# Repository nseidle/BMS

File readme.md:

Battery Management System
=======

This is a breakout board for the BQ76940. This configuration allows for 15 cells to be read. There is no safety cut off.

This is a dangerous board that exposes the user to over 48VDC and many amps. Please use responsibly.

v1 of the board is functional. Firmware is working. Most functions are written. 

-> v2 of the board has full cutoff MOSFETs and charging MOSFETs. <-

v1 of the test pack works but has multiple errors that are fixed on v2. Number labels on the cells are reversed. Cells 9 and 14 were shorted to bring the voltage back down to 48V. The clips are very close together so plastic insulators were glued in place.

License Information
-------------------

This code is public domain but you buy me a beer if you use this and we meet someday ([Beerware license](http://en.wikipedia.org/wiki/Beerware)).

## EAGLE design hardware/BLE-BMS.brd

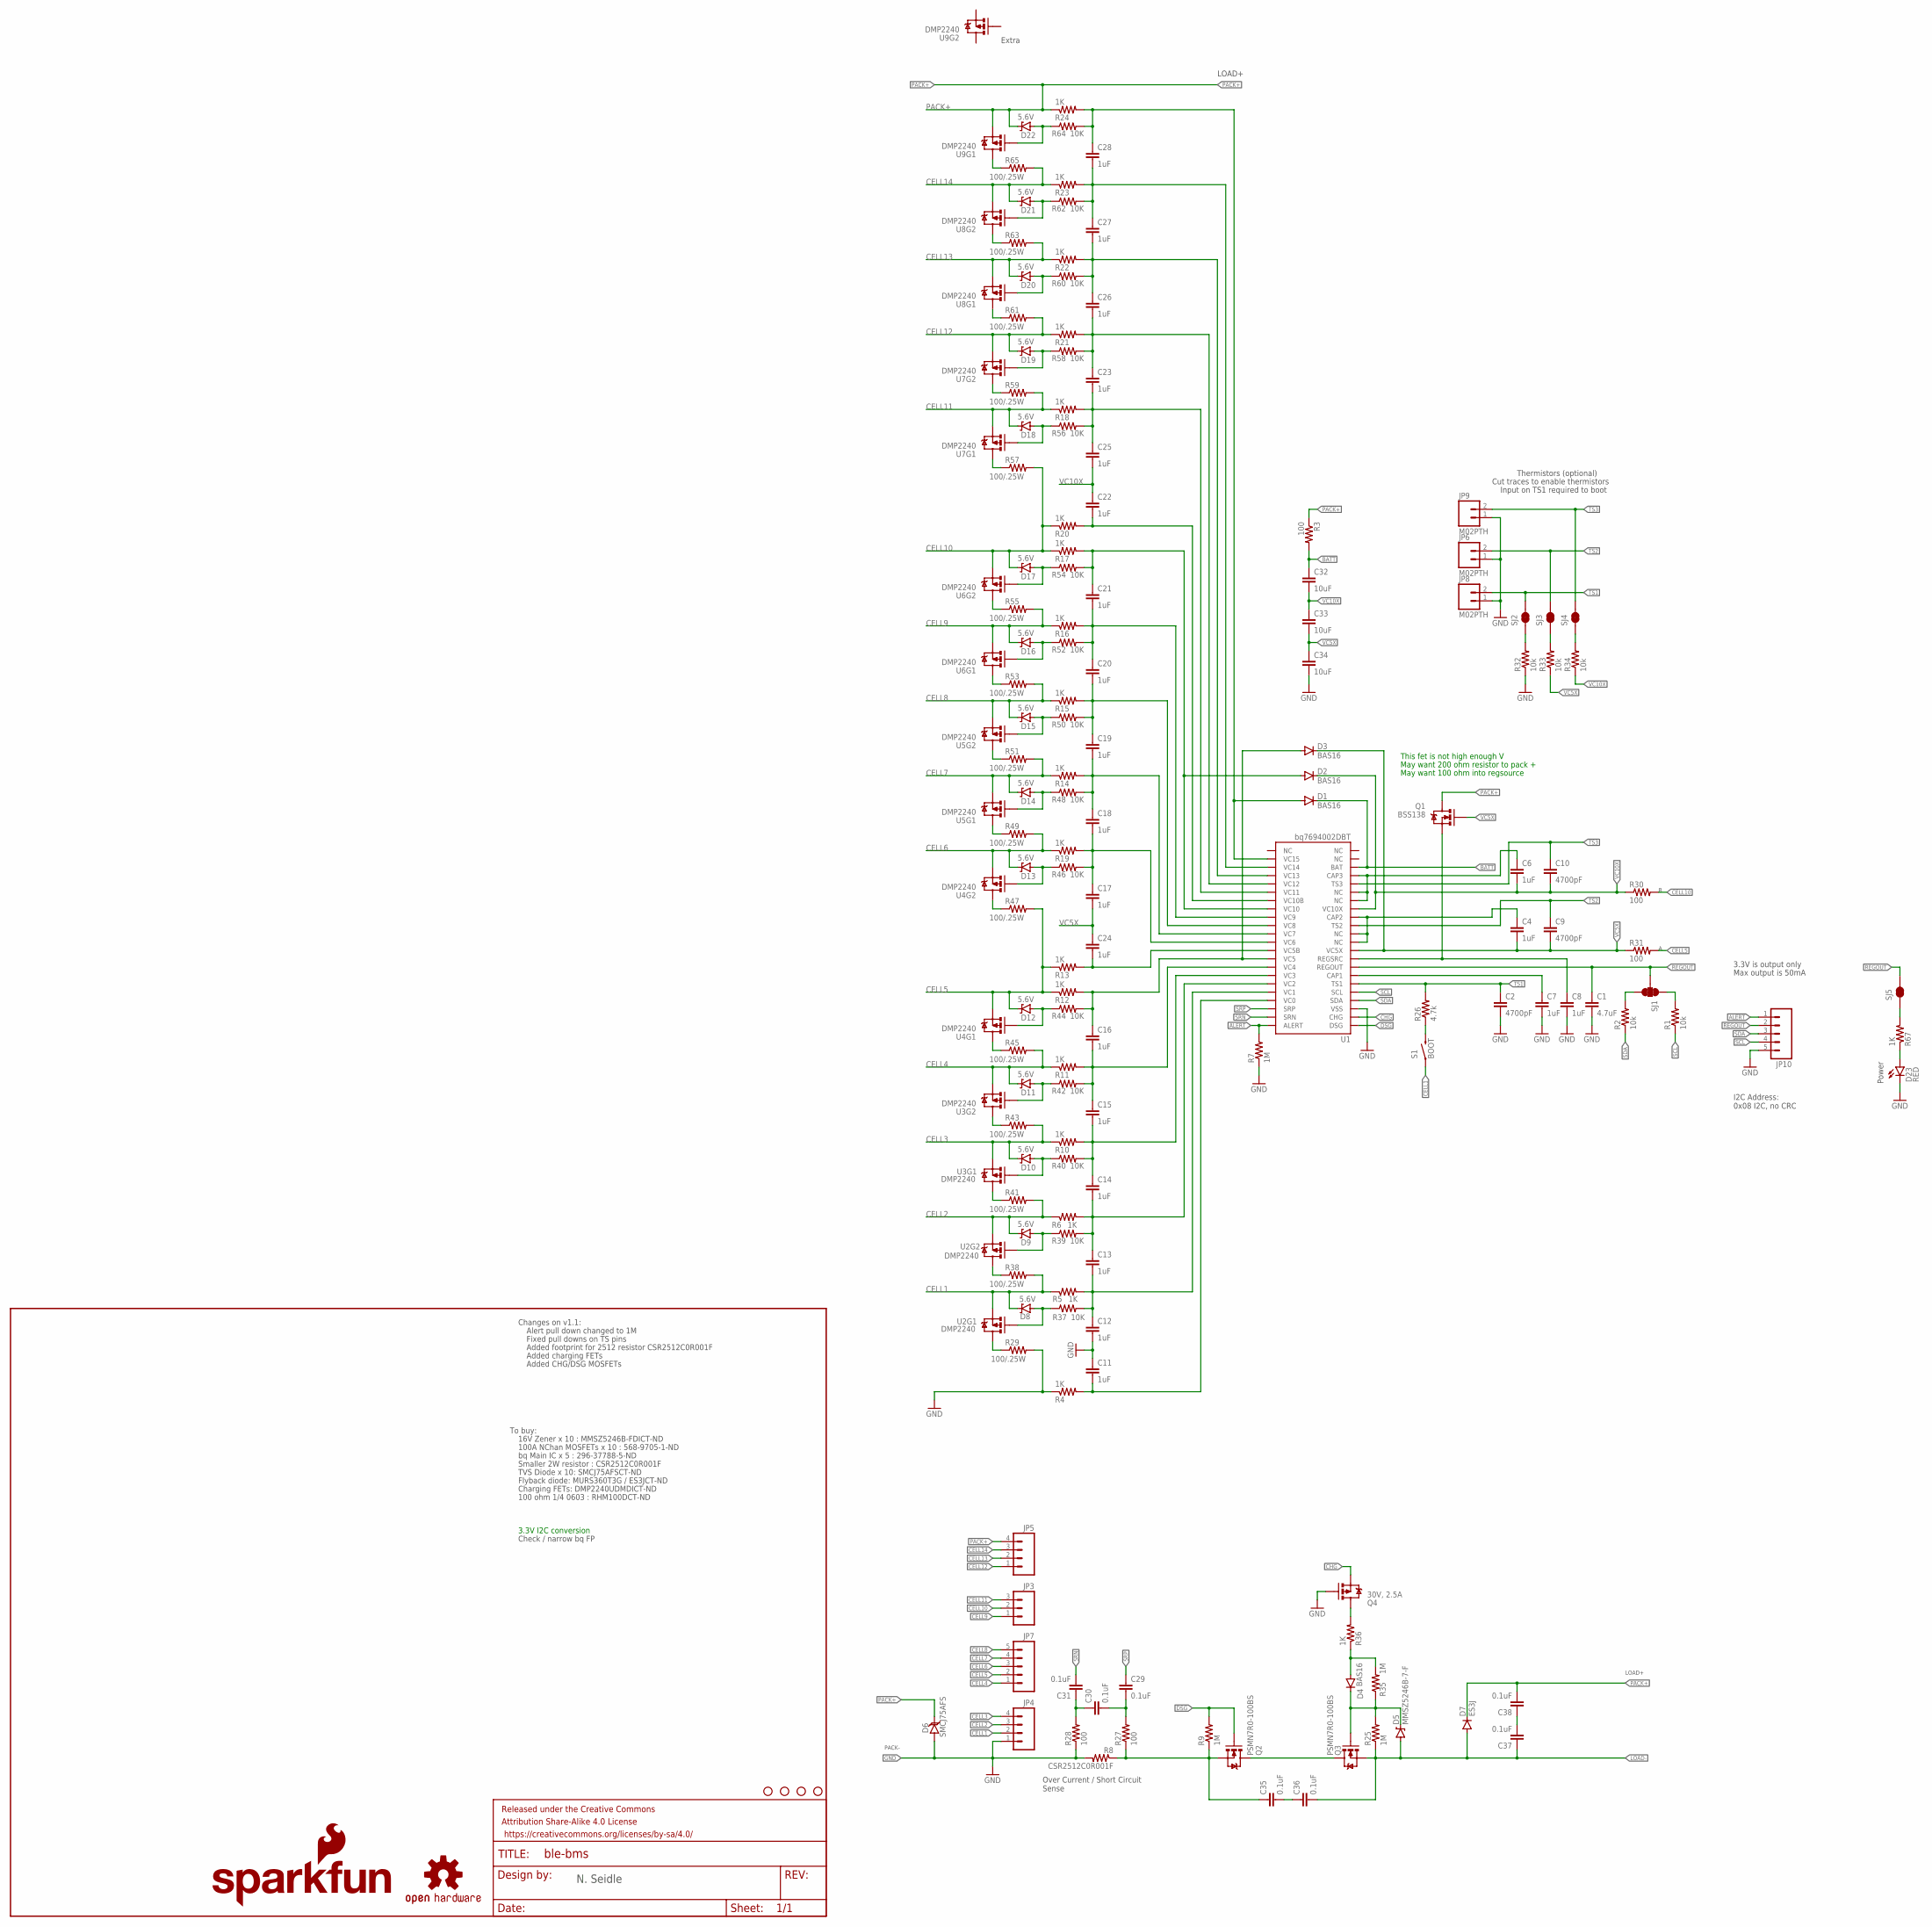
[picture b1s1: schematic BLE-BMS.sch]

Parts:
C1: 4.7uF; 0603-CAP
C2, C9, C10: 4700pF; 0603-CAP
C4, C6, C7, C8, C11, C12, C13, C14, C15, C16, C17, C18, C19, C20, C21, C22, C23, C24, C25, C26, C27, C28: 1uF; 0603-CAP
C29, C30, C31, C35, C36, C37, C38: 0.1uF; 0603-CAP
C32, C33, C34: 10uF; 1210
D1, D2, D3, D4: BAS16; SOD-323
D5: MMSZ5246B-7-F; SOD-123
D6: SMCJ75AFS; SMC
D7: ES3J; SMC
D8, D9, D10, D11, D12, D13, D14, D15, D16, D17, D18, D19, D20, D21, D22: 5.6V; SOD-323
D23: RED; LED-1206
FRAME1: FRAME-LETTER; CREATIVE_COMMONS
JP3: M03JST-PTH; JST-3-PTH
JP4, JP5: M04JST-PTH; JST-4-PTH
JP6, JP8, JP9: M02PTH; 1X02
JP7: M05JST; JST-5-PTH
JP10: M05PTH; 1X05
LOGO1: SFE_LOGO_NAME_FLAME.1_INCH; SFE_LOGO_NAME_FLAME_.1
Q1: BSS138; SOT23-3
Q2, Q3: PSMN7R0-100BS; TO-263/D2PAK
Q4: 30V, 2.5A; SOT23-3
R1, R2, R32, R33, R34: 10k; 0603-RES
R3, R27, R28, R30, R31: 100; 0603-RES
R4, R5, R6, R10, R11, R12, R13, R14, R15, R16, R17, R18, R19, R20, R21, R22, R23, R24, R36, R67: 1K; 0603-RES
R7, R9, R25, R35: 1M; 0603-RES
R8: CSR2512C0R001F; 2512
R26: 4.7k; 0603-RES
R29, R38, R41, R43, R45, R47, R49, R51, R53, R55, R57, R59, R61, R63, R65: 100/.25W; 0603-RES
R37, R39, R40, R42, R44, R46, R48, R50, R52, R54, R56, R58, R60, R62, R64: 10K; 0603-RES
S1: BOOT; TACTILE-SWITCH-1101NE
SJ1: JUMPER-PAD-3-NC_BY_TRACE; PAD-JUMPER-3-3OF3_NC_BY_TRACE_YES_SILK_FULL_BOX
SJ2, SJ3, SJ4, SJ5: JUMPER-PAD-2-NC_BY_TRACE; PAD-JUMPER-2-NC_BY_TRACE_YES_SILK
STANDOFF1, STANDOFF2, STANDOFF3, STANDOFF4: STAND-OFF
U1: bq7694002DBT; 44-TSSOP
U2, U3, U4, U5, U6, U7, U8, U9: DMP2240; SOT26
U$7: OSHW-LOGOS; OSHW-LOGO-S

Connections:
ALERT: JP10.1, R7.2, U1.44 (ALERT)
BATT: C32.1, D1.C, R3.2, U1.20 (BAT)
CAP2: C4.1, U1.11 (NC), U1.12 (NC), U1.14 (CAP2)
CAP3: C6.1, U1.16 (NC), U1.17 (NC), U1.19 (CAP3)
CELL1: D8.C, JP4.2, R5.1, R38.2, S1.1, U2.S1 (S)
CELL2: D9.C, JP4.3, R6.1, R41.2, U2.S2 (S)
CELL3: D10.C, JP4.4, R10.1, R43.2, U3.S1 (S)
CELL4: D11.C, JP7.1, R11.1, R45.2, U3.S2 (S)
CELL5: D12.C, JP7.2, R12.1, R13.1, R31.2, R47.2, U4.S1 (S)
CELL6: D13.C, JP7.3, R19.1, R49.2, U4.S2 (S)
CELL7: D14.C, JP7.4, R14.1, R51.2, U5.S1 (S)
CELL8: D15.C, JP7.5, R15.1, R53.2, U5.S2 (S)
CELL9: D16.C, JP3.1, R16.1, R55.2, U6.S1 (S)
CELL10: D17.C, JP3.2, R17.1, R20.1, R30.2, R57.2, U6.S2 (S)
CELL11: D18.C, JP3.3, R18.1, R59.2, U7.S1 (S)
CELL12: D19.C, JP5.1, R21.1, R61.2, U7.S2 (S)
CELL13: D20.C, JP5.2, R22.1, R63.2, U8.S1 (S)
CELL14: D21.C, JP5.3, R23.1, R65.2, U8.S2 (S)
CHG: Q4.2 (S), U1.2 (CHG)
CHG_CTL: D4.C, D5.C, Q3.1 (G), R25.2, R35.1
DSG: Q2.1 (G), R9.2, U1.1 (DSG)
GND: C1.2, C2.2, C7.2, C8.2, C11.1, C12.2, C34.2, D6.A, D23.C, JP4.1, JP6.1, JP8.1, JP9.1, JP10.5, Q4.1 (G), R4.1, R7.1, R8.2, R28.1, R29.2, R32.1, U1.3 (VSS)
LOAD1: Q2.2 (D), Q3.2 (D)
LOAD2: C35.1, Q2.3 (S), R8.1, R9.1, R27.1
LOAD-: C36.2, C37.1, D5.A, D7.A, Q3.3 (S), R25.1
unnamed: D8.A, R37.1, U2.G1 (G)
unnamed: Q4.3 (D), R36.2
unnamed: R32.2, SJ2.1
unnamed: R29.1, U2.D1 (D)
unnamed: D9.A, R39.1, U2.G2 (G)
unnamed: C35.2, C36.1
unnamed: D4.A, R35.2, R36.1
unnamed: R38.1, U2.D2 (D)
unnamed: C37.2, C38.1
unnamed: R2.2, SJ1.3
unnamed: R1.2, SJ1.1
unnamed: D10.A, R40.1, U3.G1 (G)
unnamed: R41.1, U3.D1 (D)
unnamed: D11.A, R42.1, U3.G2 (G)
unnamed: R43.1, U3.D2 (D)
unnamed: D12.A, R44.1, U4.G1 (G)
unnamed: R45.1, U4.D1 (D)
unnamed: D13.A, R46.1, U4.G2 (G)
unnamed: R47.1, U4.D2 (D)
unnamed: R49.1, U5.D1 (D)
unnamed: D14.A, R48.1, U5.G1 (G)
unnamed: R51.1, U5.D2 (D)
unnamed: D15.A, R50.1, U5.G2 (G)
unnamed: R33.2, SJ3.1
unnamed: C7.1, U1.7 (CAP1)
unnamed: R26.1, S1.2
unnamed: R34.2, SJ4.1
unnamed: C29.2, C30.2, R27.2
unnamed: C30.1, C31.1, R28.2
unnamed: R53.1, U6.D1 (D)
unnamed: D16.A, R52.1, U6.G1 (G)
unnamed: D17.A, R54.1, U6.G2 (G)
unnamed: R55.1, U6.D2 (D)
unnamed: D18.A, R56.1, U7.G1 (G)
unnamed: R57.1, U7.D1 (D)
unnamed: D19.A, R58.1, U7.G2 (G)
unnamed: R59.1, U7.D2 (D)
unnamed: D20.A, R60.1, U8.G1 (G)
unnamed: R61.1, U8.D1 (D)
unnamed: D21.A, R62.1, U8.G2 (G)
unnamed: R63.1, U8.D2 (D)
unnamed: D22.A, R64.1, U9.G1 (G)
unnamed: R65.1, U9.D1 (D)
unnamed: D23.A, R67.1
unnamed: R67.2, SJ5.1
PACK+: C38.2, D6.C, D7.C, D22.C, JP5.4, Q1.3 (D), R3.1, R24.1, U9.S1 (S)
REGOUT: C1.1, JP10.2, SJ1.2, SJ5.2, U1.8 (REGOUT)
REGSRC: C8.1, Q1.2 (S), U1.9 (REGSRC)
SCL: JP10.4, R1.1, U1.5 (SCL)
SDA: JP10.3, R2.1, U1.4 (SDA)
SRN: C31.2, U1.43 (SRN)
SRP: C29.1, U1.42 (SRP)
TS1: C2.1, JP8.2, R26.2, SJ2.2, U1.6 (TS1)
TS2: C9.1, JP6.2, SJ3.2, U1.13 (TS2)
TS3: C10.1, JP9.2, SJ4.2, U1.18 (TS3)
VC0: C11.2, R4.2, U1.41 (VC0)
VC1: C12.1, C13.2, R5.2, R37.2, U1.40 (VC1)
VC2: C13.1, C14.2, R6.2, R39.2, U1.39 (VC2)
VC3: C14.1, C15.2, R10.2, R40.2, U1.38 (VC3)
VC4: C15.1, C16.2, R11.2, R42.2, U1.37 (VC4)
VC5: C16.1, D3.A, R12.2, R44.2, U1.36 (VC5)
VC5B: C24.2, R13.2, U1.35 (VC5B)
VC5X: C4.2, C9.2, C17.2, C24.1, C33.2, C34.1, D3.C, Q1.1 (G), R31.1, R33.1, U1.10 (VC5X)
VC6: C17.1, C18.2, R19.2, R46.2, U1.34 (VC6)
VC7: C18.1, C19.2, R14.2, R48.2, U1.33 (VC7)
VC8: C19.1, C20.2, R15.2, R50.2, U1.32 (VC8)
VC9: C20.1, C21.2, R16.2, R52.2, U1.31 (VC9)
VC10: C21.1, D2.A, R17.2, R54.2, U1.30 (VC10)
VC10B: C22.2, R20.2, U1.29 (VC10B)
VC10X: C6.2, C10.2, C22.1, C25.2, C32.2, C33.1, D2.C, R30.1, R34.1, U1.15 (VC10X)
VC11: C23.2, C25.1, R18.2, R56.2, U1.28 (VC11)
VC12: C23.1, C26.2, R21.2, R58.2, U1.27 (VC12)
VC13: C26.1, C27.2, R22.2, R60.2, U1.26 (VC13)
VC14: C27.1, C28.2, R23.2, R62.2, U1.25 (VC14)
VC15: C28.1, D1.A, R24.2, R64.2, U1.24 (VC15)

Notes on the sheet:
Thermistors (optional)
Over Current / Short Circuit Sense
Cut traces to enable thermistors
Input on TS1 required to boot
Added footprint for 2512 resistor CSR2512C0R001F
3.3V I2C conversion
I2C Address: 0x08 I2C, no CRC
This fet is not high enough V
May want 200 ohm resistor to pack +
May want 100 ohm into regsource
Changes on v1.1:
Alert pull down changed to 1M
Fixed pull downs on TS pins
PACK-
To buy:
16V Zener x 10 : MMSZ5246B-FDICT-ND
100A NChan MOSFETs x 10 : 568-9705-1-ND
bq Main IC x 5 : 296-37788-5-ND
Smaller 2W resistor : CSR2512C0R001F
TVS Diode x 10: SMCJ75AFSCT-ND
Flyback diode: MURS360T3G / ES3JCT-ND
LOAD+
Charging FETs: DMP2240UDMDICT-ND
100 ohm 1/4 0603 : RHM100DCT-ND
Check / narrow bq FP
N. Seidle
Added charging FETs
Added CHG/DSG MOSFETs
Extra
3.3V is output only
Max output is 50mA
Power

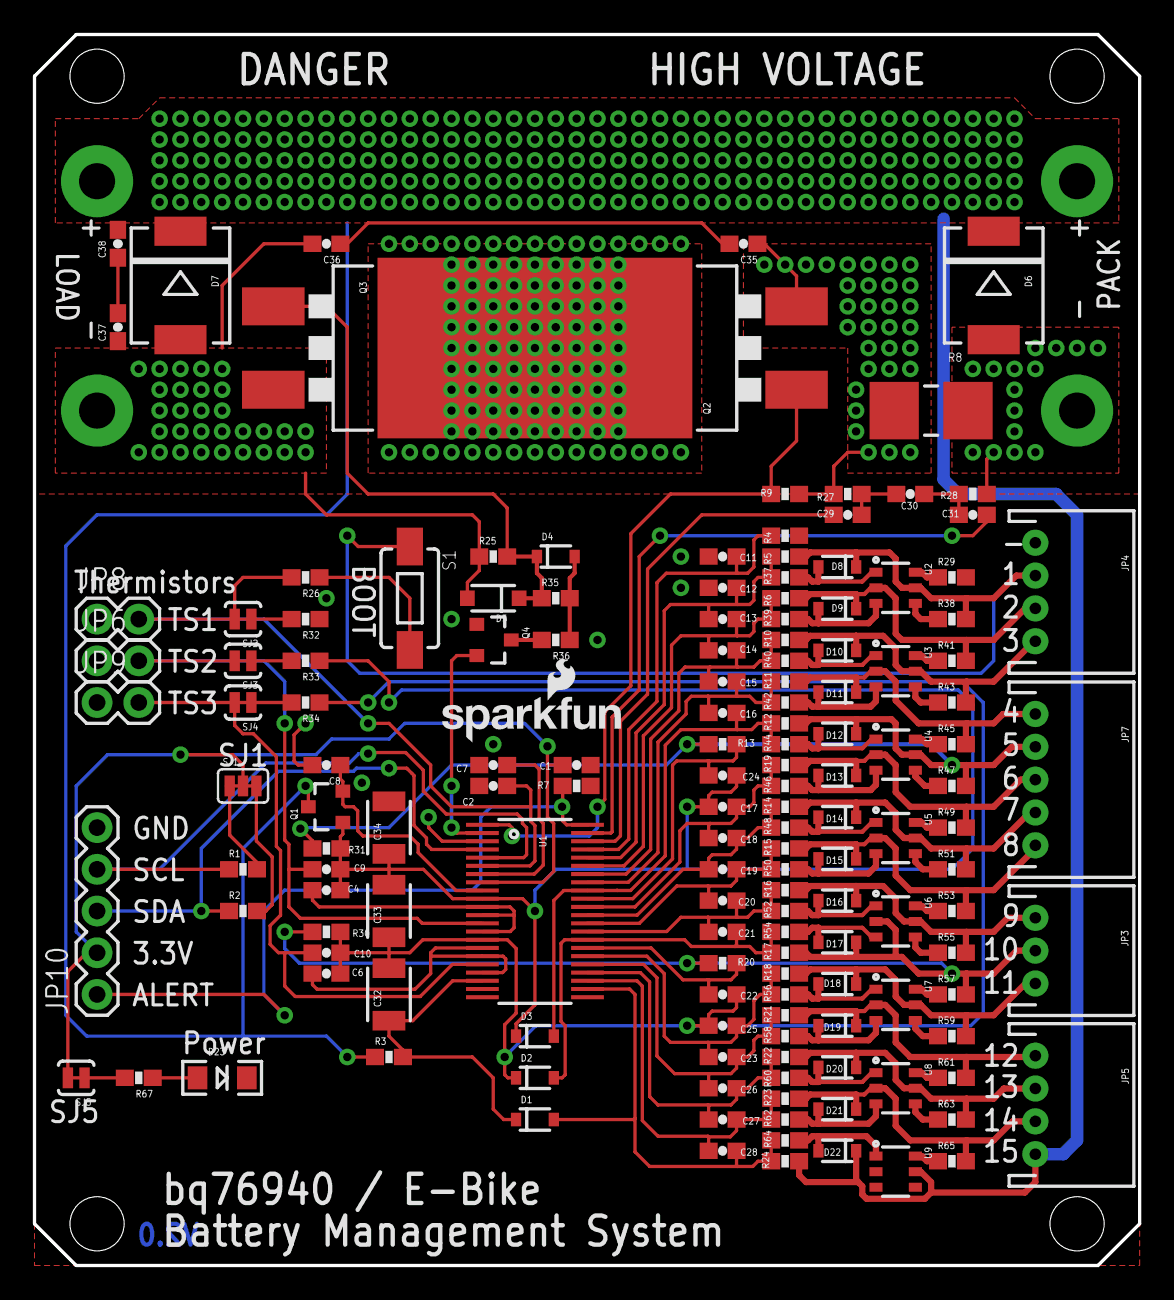
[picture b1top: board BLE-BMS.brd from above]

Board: 2 copper layers, 67.3 x 75.0 mm, 159 parts (1 on the bottom side), 100 nets.

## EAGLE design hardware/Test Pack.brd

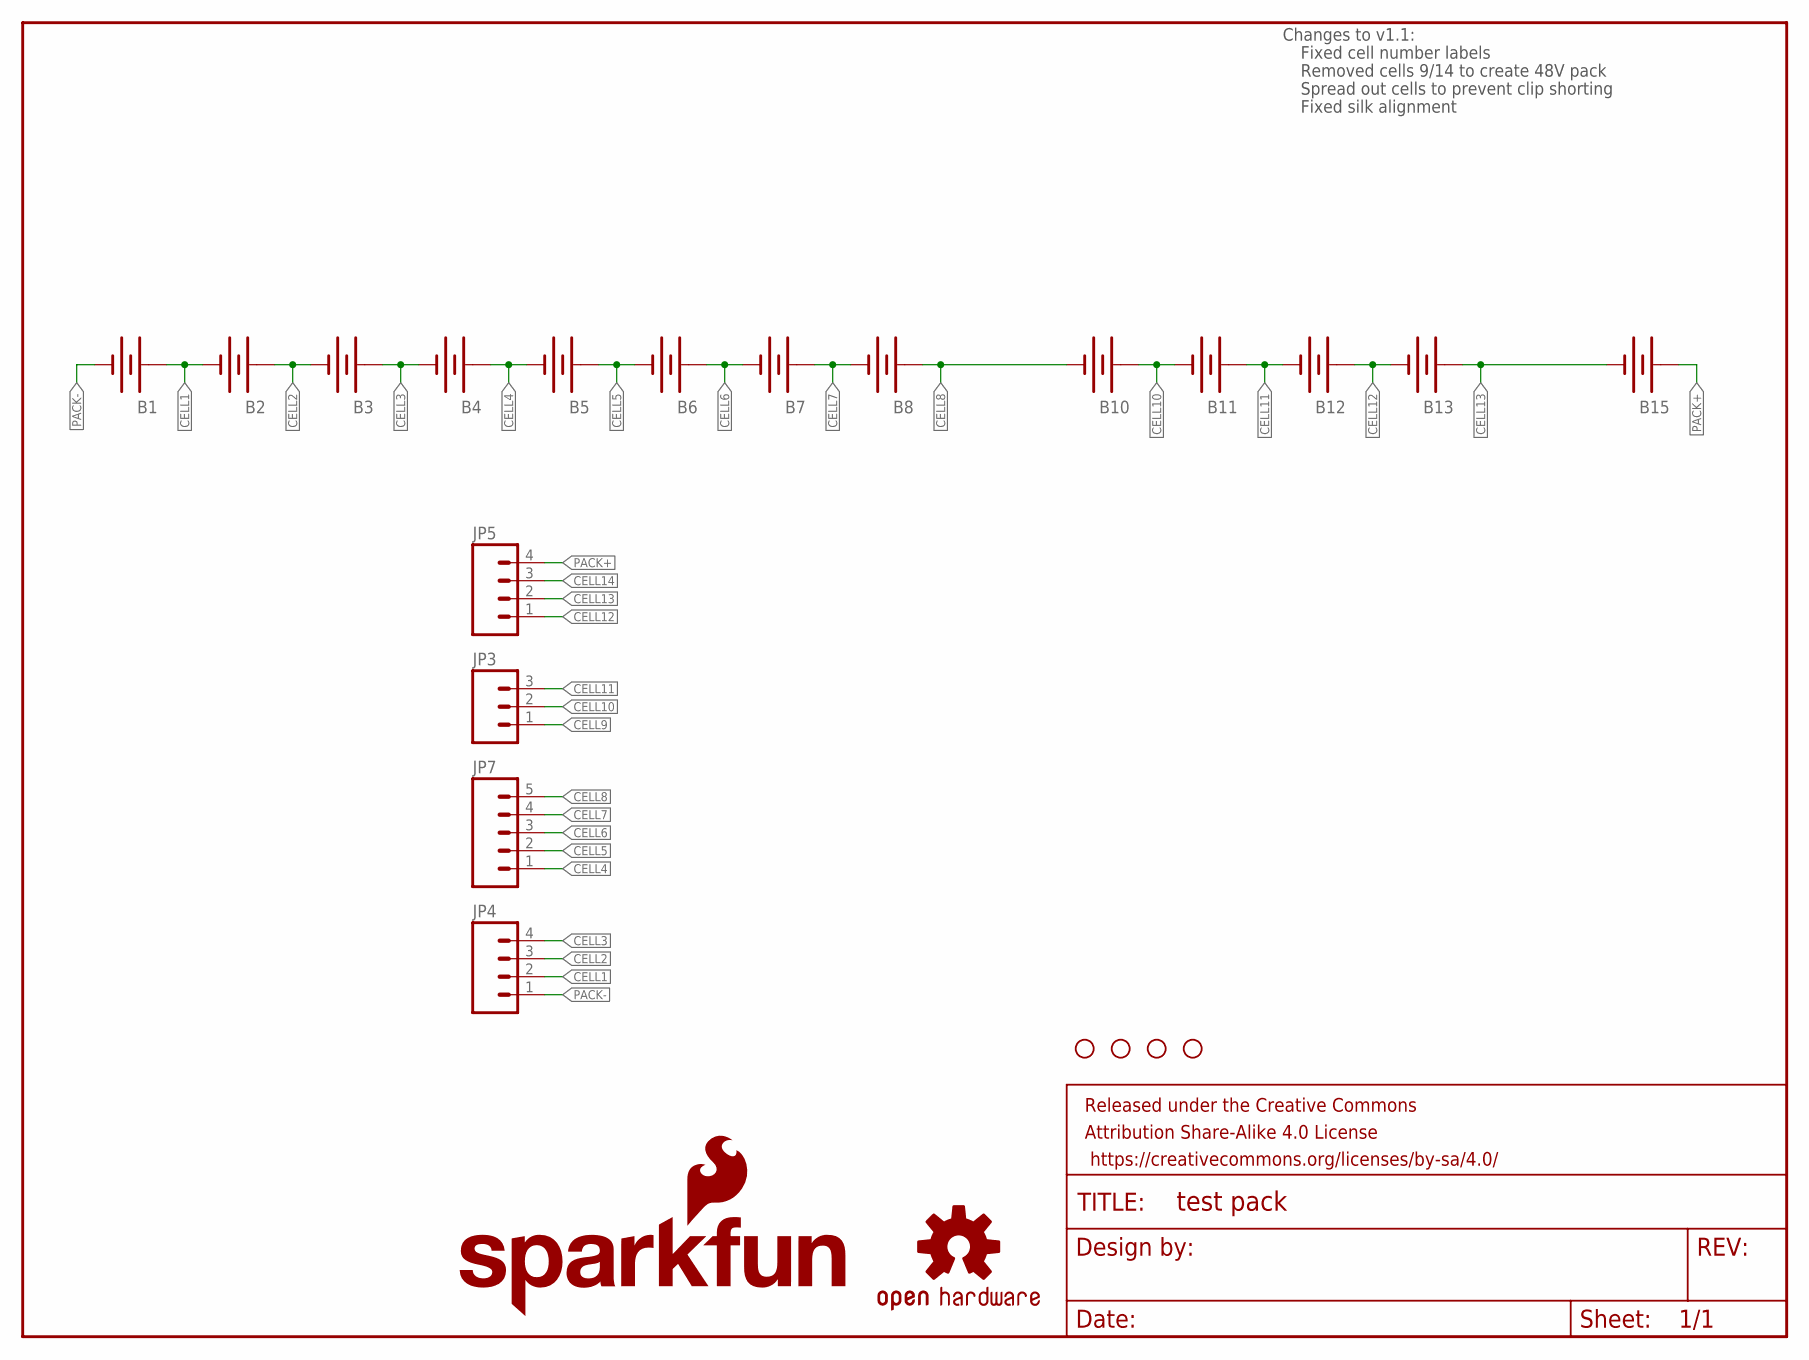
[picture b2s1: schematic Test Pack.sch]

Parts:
B1, B2, B3, B4, B5, B6, B7, B8, B10, B11, B12, B13, B15: BATTERY18650; BATTERY_18650-HOLDER
FRAME1: FRAME-LETTER; CREATIVE_COMMONS
JP3: M03JST-PTH; JST-3-PTH
JP4, JP5: M04JST-PTH; JST-4-PTH
JP7: M05JST; JST-5-PTH
LOGO1: SFE_LOGO_NAME_FLAME.1_INCH; SFE_LOGO_NAME_FLAME_.1
STANDOFF1, STANDOFF2, STANDOFF3, STANDOFF4: STAND-OFF
U$7: OSHW-LOGOS; OSHW-LOGO-S

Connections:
CELL1: B1.PWR@1 (+), B2.GND@1 (-), JP4.2
CELL2: B2.PWR@1 (+), B3.GND@1 (-), JP4.3
CELL3: B3.PWR@1 (+), B4.GND@1 (-), JP4.4
CELL4: B4.PWR@1 (+), B5.GND@1 (-), JP7.1
CELL5: B5.PWR@1 (+), B6.GND@1 (-), JP7.2
CELL6: B6.PWR@1 (+), B7.GND@1 (-), JP7.3
CELL7: B7.PWR@1 (+), B8.GND@1 (-), JP7.4
CELL8: B8.PWR@1 (+), B10.GND@1 (-), JP7.5
CELL9: JP3.1
CELL10: B10.PWR@1 (+), B11.GND@1 (-), JP3.2
CELL11: B11.PWR@1 (+), B12.GND@1 (-), JP3.3
CELL12: B12.PWR@1 (+), B13.GND@1 (-), JP5.1
CELL13: B13.PWR@1 (+), B15.GND@1 (-), JP5.2
CELL14: JP5.3
PACK+: B15.PWR@1 (+), JP5.4
PACK-: B1.GND@1 (-), JP4.1

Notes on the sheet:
Changes to v1.1:
Fixed cell number labels
Removed cells 9/14 to create 48V pack
Spread out cells to prevent clip shorting
Fixed silk alignment

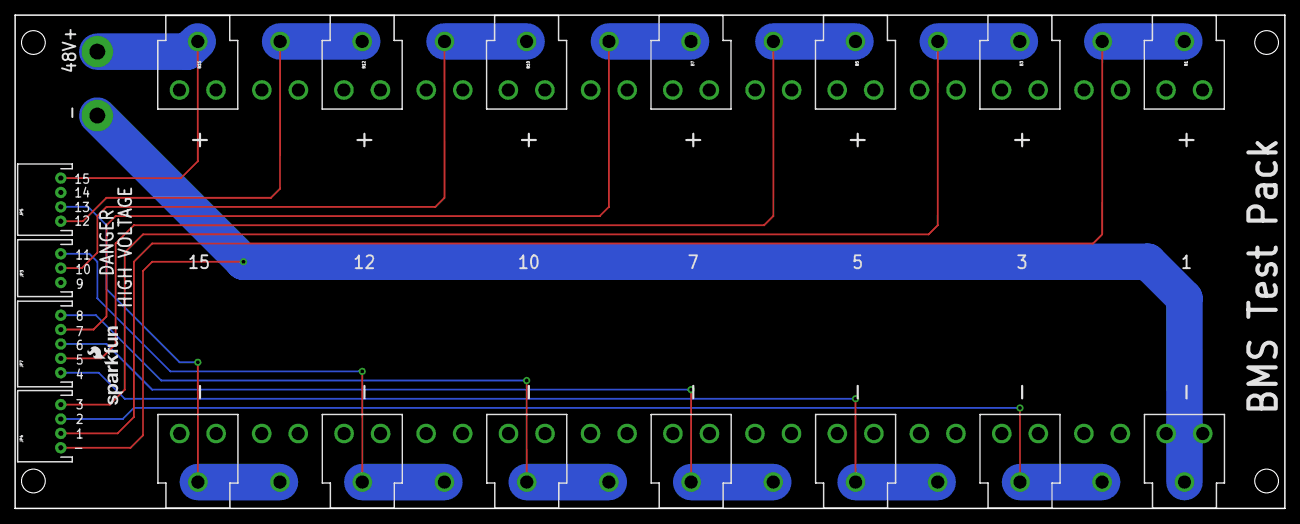
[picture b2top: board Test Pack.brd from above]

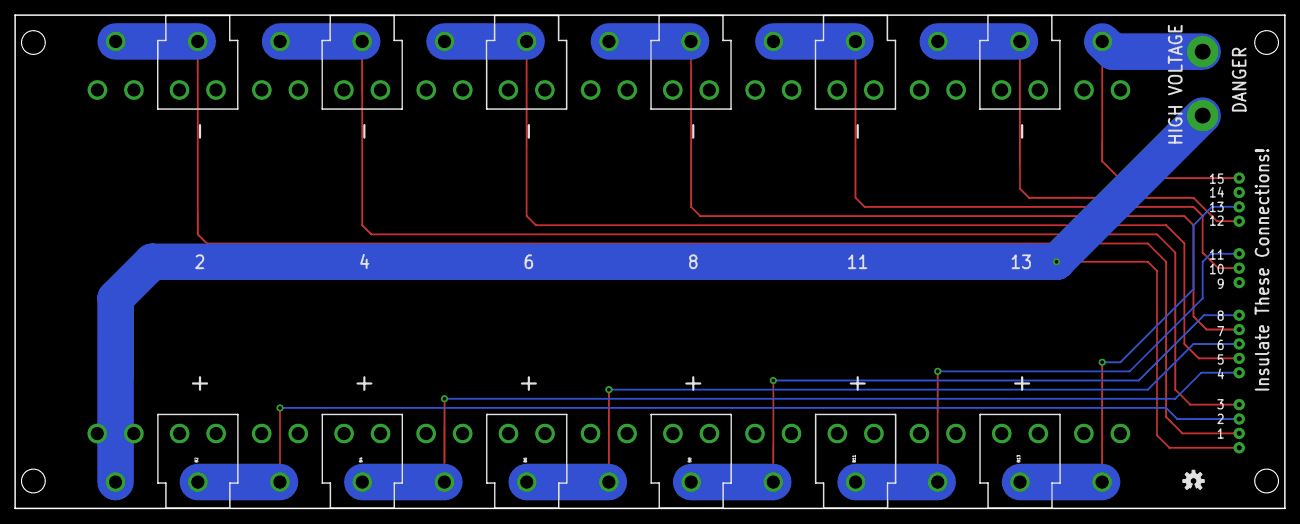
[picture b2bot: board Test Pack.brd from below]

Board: 2 copper layers, 176.5 x 68.6 mm, 24 parts (7 on the bottom side), 14 nets.

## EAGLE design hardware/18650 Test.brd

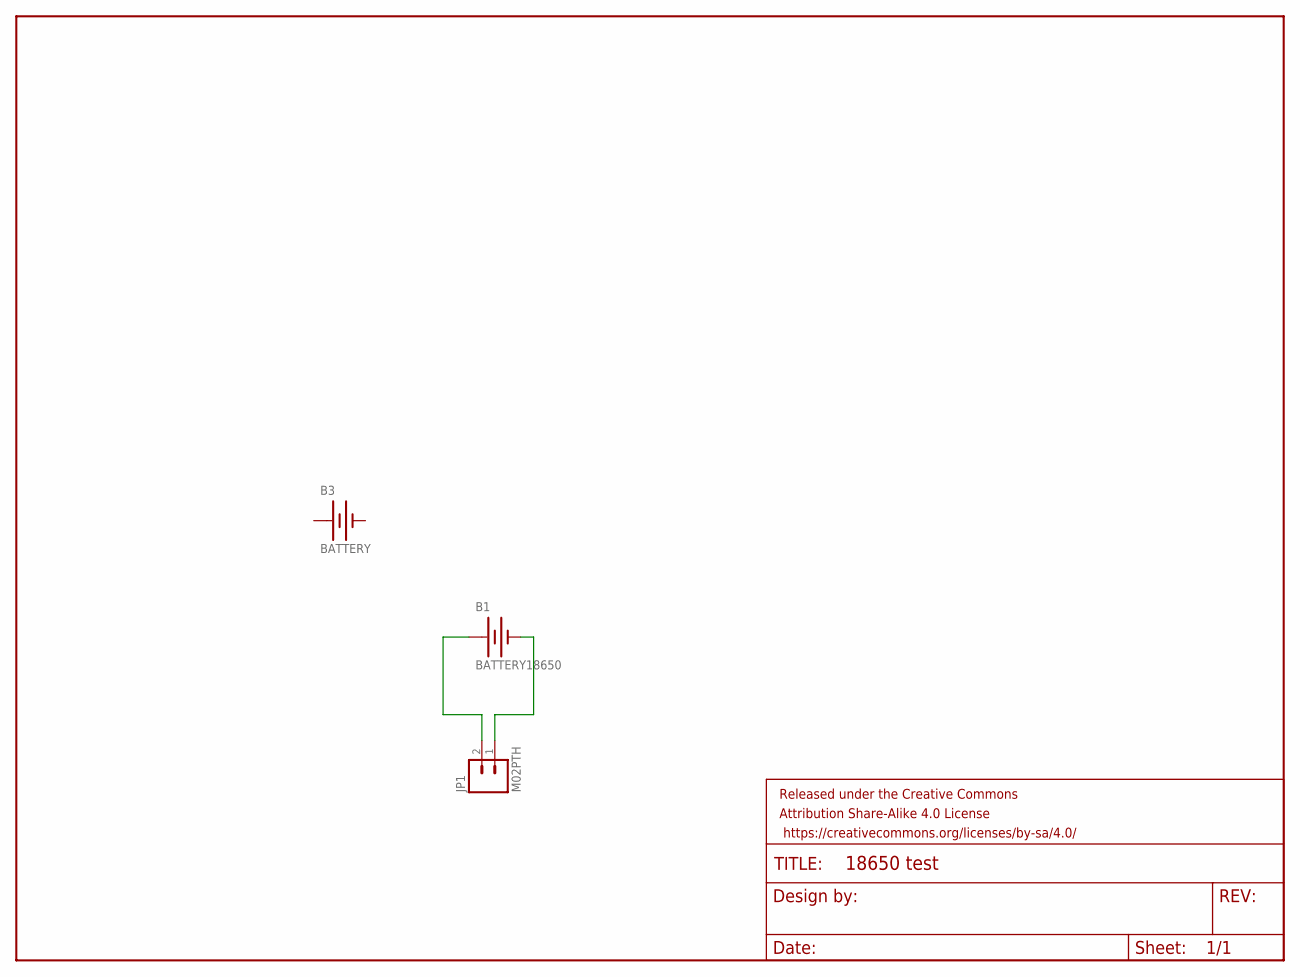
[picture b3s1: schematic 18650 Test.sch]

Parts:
B1: BATTERY18650; 18650-HOLDER
B3: BATTERY; 18650-TEST
FRAME1: FRAME-LETTER; CREATIVE_COMMONS
JP1: M02PTH; 1X02

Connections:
+: B3.PWR@4 (+)
-: B3.PWR@3 (-)
GND: B1.GND@1 (-), JP1.1
VCC: B1.PWR@1 (+), JP1.2

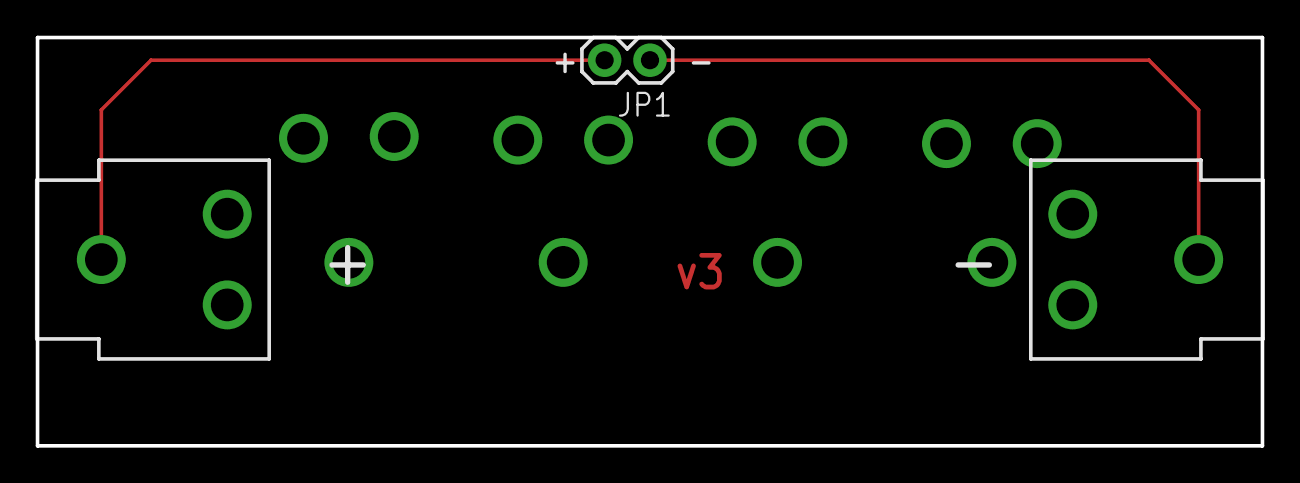
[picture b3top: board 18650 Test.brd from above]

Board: 2 copper layers, 68.6 x 22.9 mm, 4 parts (1 on the bottom side), 2 nets.

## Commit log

2014-09-08 :lollipop: Added .gitattributes & .gitignore files
2014-09-08 Initial commit
    Breakout for the BQ76940 battery monitor.
2014-09-08 Adding production part #s.
2014-09-08 Adding readme and layout image.
2014-10-29 Firmware, test pack layouts.
    Firmware is mostly working! Layouts are pretty good.
2014-10-29 Removing Eagle backup files.
2014-11-15 v2 with Charge/Discharge MOSFET control and cell balancing
    Many changes. Added large MOSFETs and pack interface circuitry. Added
    small MOSFETs for individual cell balancing/charging. Corrected
    Thermistor pull down error. All FPs pass 1:1 check.
2014-11-15 Adding assembled v1 image
2014-11-15 Adding photos and updating readme.
2015-09-29 Adding example project from Hans Maulwurf
2018-01-26 Fixing readme

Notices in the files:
parts and their libraries:
SparkFun-Aesthetics: Licensing: CC v3.0 Share-Alike You are welcome to use this library for commercial purposes.
SparkFun-Aesthetics: Released under the Creative Commons Attribution Share-Alike 4.0 License
SparkFun-Aesthetics: https://creativecommons.org/licenses/by-sa/4.0
